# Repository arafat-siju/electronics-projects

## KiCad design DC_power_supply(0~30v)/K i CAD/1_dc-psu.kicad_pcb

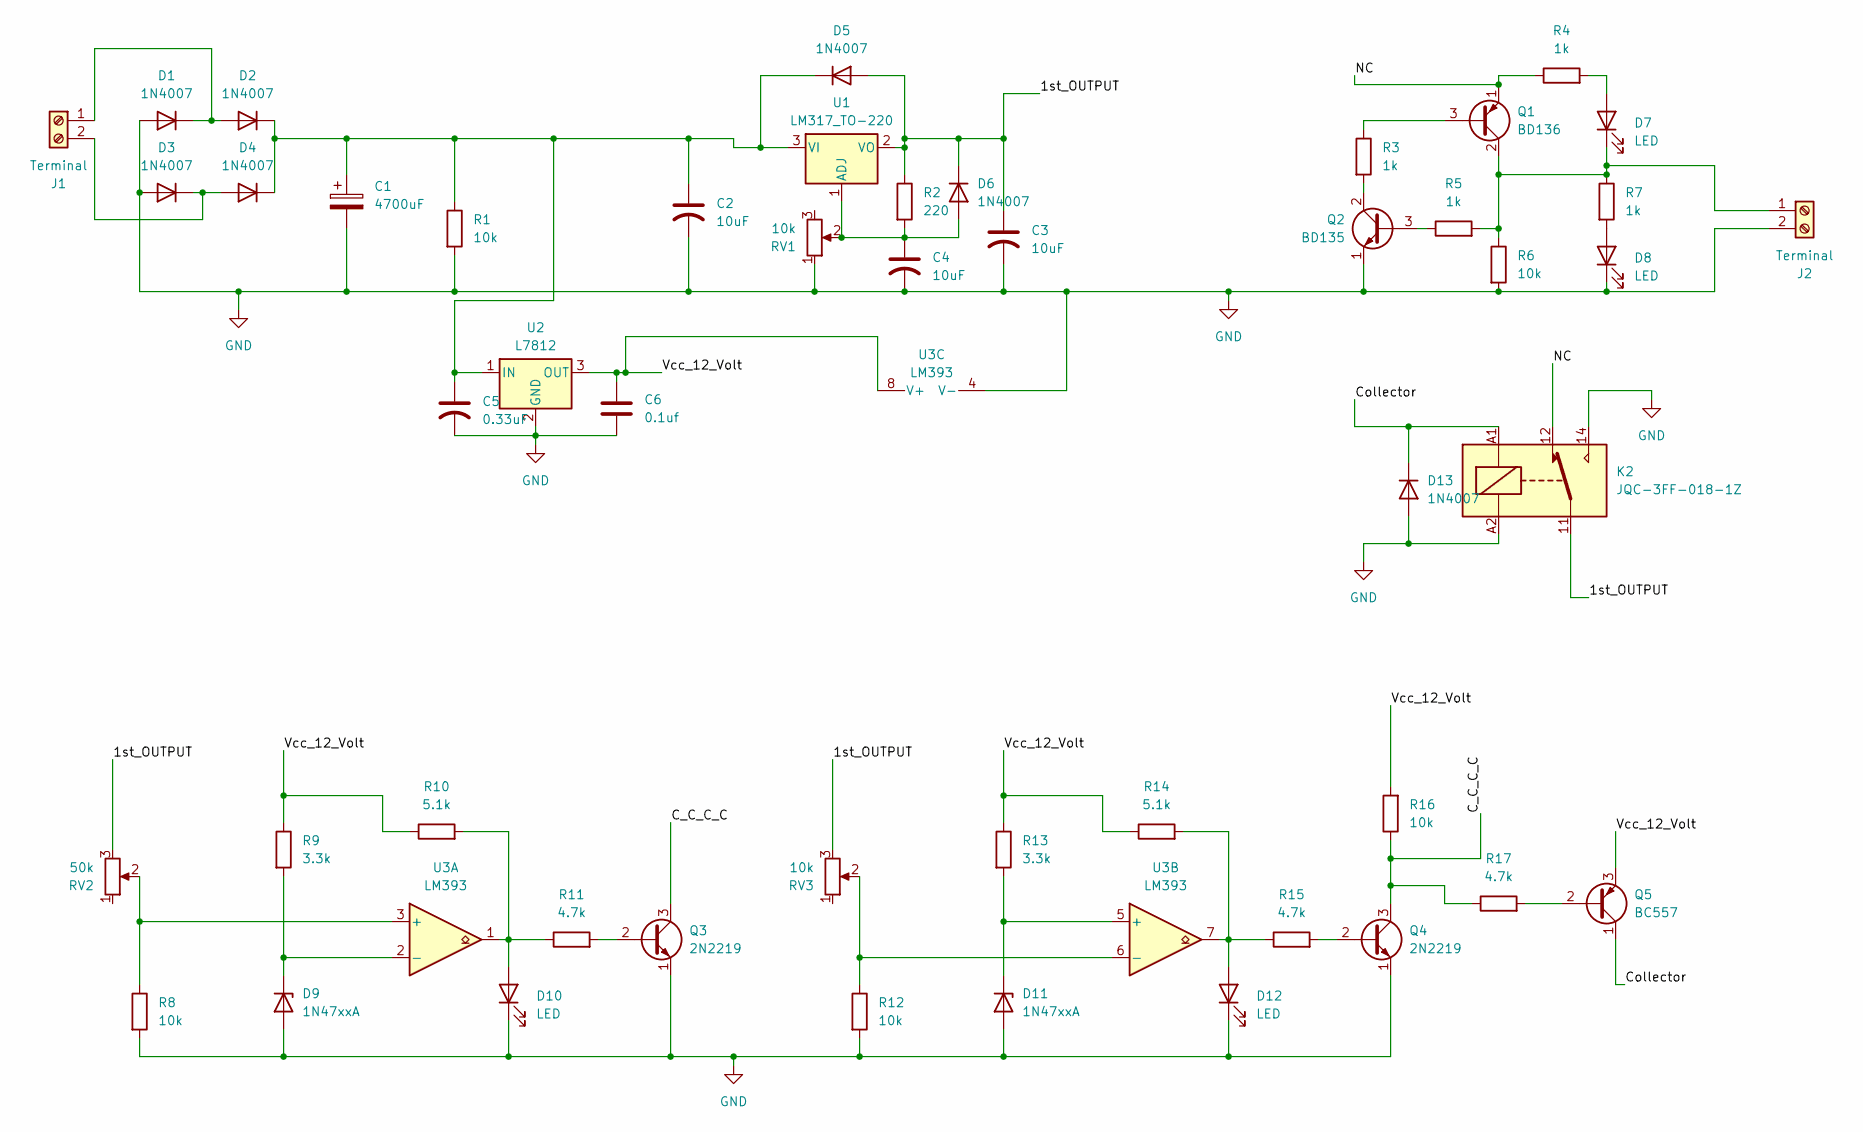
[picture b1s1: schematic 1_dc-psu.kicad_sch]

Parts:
C1: 4700uF; CP_Radial_D18.0mm_P7.50mm
C2, C3, C4: 10uF; CP_Radial_D5.0mm_P2.50mm
C5: 0.33uF; CP_Radial_D5.0mm_P2.50mm
C6: 0.1uf; C_Disc_D3.0mm_W1.6mm_P2.50mm
D1, D2, D3, D4, D5, D6, D13: 1N4007; D_DO-41_SOD81_P10.16mm_Horizontal
D7, D8, D10, D12: LED; LED_D3.0mm
D9, D11: 1N47xxA; D_DO-41_SOD81_P10.16mm_Horizontal
J1, J2: Terminal; TerminalBlock_MaiXu_MX126-5.0-02P_1x02_P5.00mm
K2: JQC-3FF-018-1Z; Relay_SPDT_Hongfa_JQC-3FF_0XX-1Z
Q1: BD136; TO-126-3_Vertical
Q2: BD135; TO-126-3_Vertical
Q3, Q4: 2N2219; TO-39-3
Q5: BC557; TO-92_Inline
R1, R6, R8, R12, R16: 10k; R_Axial_DIN0309_L9.0mm_D3.2mm_P12.70mm_Horizontal
R2: 220; R_Axial_DIN0309_L9.0mm_D3.2mm_P12.70mm_Horizontal
R3, R4, R5, R7: 1k; R_Axial_DIN0309_L9.0mm_D3.2mm_P12.70mm_Horizontal
R9, R13: 3.3k; R_Axial_DIN0309_L9.0mm_D3.2mm_P12.70mm_Horizontal
R10, R14: 5.1k; R_Axial_DIN0309_L9.0mm_D3.2mm_P12.70mm_Horizontal
R11, R15, R17: 4.7k; R_Axial_DIN0309_L9.0mm_D3.2mm_P12.70mm_Horizontal
RV1: 10k; Potentiometer_Alps_RK163_Single_Horizontal
RV2: 50k; Potentiometer_Bourns_3386F_Vertical
RV3: 10k; Potentiometer_Bourns_3386F_Vertical
U1: LM317_TO-220; TO-220-3_Vertical
U2: L7812; TO-220-3_Vertical
U3: LM393; DIP-8_W7.62mm_LongPads

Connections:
/1st_OUTPUT: C3.1, D5.2 (A), D6.1 (K), K2.11, R2.1, RV2.3, RV3.3, U1.2 (VO)
/C_C_C_C: Q3.3 (C), Q4.3 (C), R16.1, R17.1
/Collector: D13.1 (K), K2.A1, Q5.1 (C)
/NC: K2.12, Q1.1 (E), R4.1
/Vcc_12_Volt: C6.1, Q5.3 (E), R9.1, R10.1, R13.1, R14.1, R16.2, U2.3 (OUT), U3.8 (V+)
GND: C1.2, C2.2, C3.2, C4.2, C5.2, C6.2, D1.2 (A), D3.2 (A), D8.1 (K), D9.2 (A), D10.1 (K), D11.2 (A), D12.1 (K), D13.2 (A), J2.2, K2.14, K2.A2, Q2.1 (E), Q3.1 (E), Q4.1 (E), R1.2, R6.2, R8.2, R12.2, RV1.1, U2.2 (GND), U3.4 (V-)
unnamed: D1.1 (K), D2.2 (A), J1.1
unnamed: C1.1, C2.1, C5.1, D2.1 (K), D4.1 (K), D5.1 (K), R1.1, U1.3 (VI), U2.1 (IN)
unnamed: D3.1 (K), D4.2 (A), J1.2
unnamed: C4.1, D6.2 (A), R2.2, RV1.2, U1.1 (ADJ)
unnamed: D7.2 (A), R4.2
unnamed: D7.1 (K), J2.1, Q1.2 (C), R5.2, R6.1, R7.1
unnamed: D8.2 (A), R7.2
unnamed: D9.1 (K), R9.2, U3.2 (-)
unnamed: D10.2 (A), R10.2, R11.1, U3.1
unnamed: D11.1 (K), R13.2, U3.5 (+)
unnamed: D12.2 (A), R14.2, R15.1, U3.7
unnamed: Q1.3 (B), R3.1
unnamed: Q2.3 (B), R5.1
unnamed: Q2.2 (C), R3.2
unnamed: Q3.2 (B), R11.2
unnamed: Q4.2 (B), R15.2
unnamed: Q5.2 (B), R17.2
unnamed: R8.1, RV2.2, U3.3 (+)
unnamed: R12.1, RV3.2, U3.6 (-)

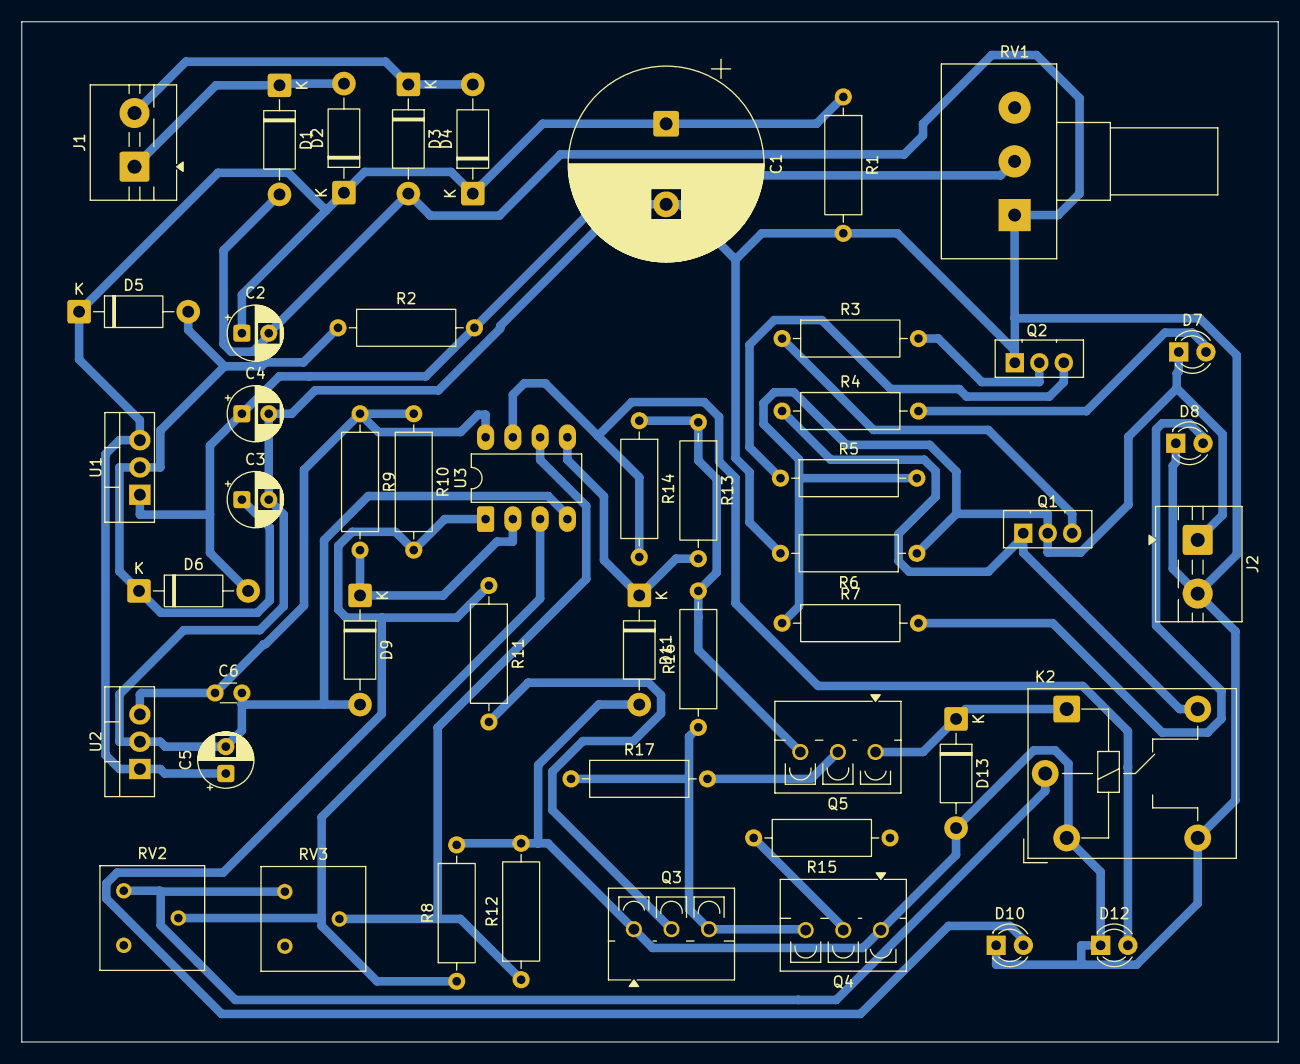
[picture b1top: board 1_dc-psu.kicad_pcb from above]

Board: 2 copper layers, 117.0 x 95.0 mm, 50 parts (0 on the bottom side), 25 nets.

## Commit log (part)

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2026-05-22 moved to new dir
2026-05-22 README.md
    Added detailed project overview, objectives, and team members for the Op-Amp Based Function Generator.
